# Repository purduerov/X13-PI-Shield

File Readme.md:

# Readme for X13-PI-Shield

Whenever you make a new part, download the datasheet and save it here _**and**_ with the part in the parts library

Always pull other people's changes before beginning to work
`git pull`

Be sure to push your changes after  working on them. Run:
1. `git add .` to add any files in this directory or a subdirectory
or `git add -u` to add any modified files
2. (Optional) `git clean -nX` to see what ignored files can be removed
	`git clean -fX` removes ignored files (Eagle backups)
3. `git commit -m "helpful commit message"` with a description of the work that you did
4. `git push` to push your work to github

Other helpful commands
* `git status` says information about modified and staged files
* `git log` shows the recent commits of the repository
* `git log filename.extension` show the recent commits for just that file
* `git checkout first-couple-letter-of-commit-id` lets you go back to a previous version
* `git checkout master` brings you back to the latest commit
* `git tag` lists the tags
* `git tag -a orderX -m "the version of the board placed for the X'th order"` tag a specific commit
* `git push --tags` needed to push tags to remote
* `git show orderX` show the commit log for the given tag
* `git checkout orderX` go back and interact with the files at the tagged commit

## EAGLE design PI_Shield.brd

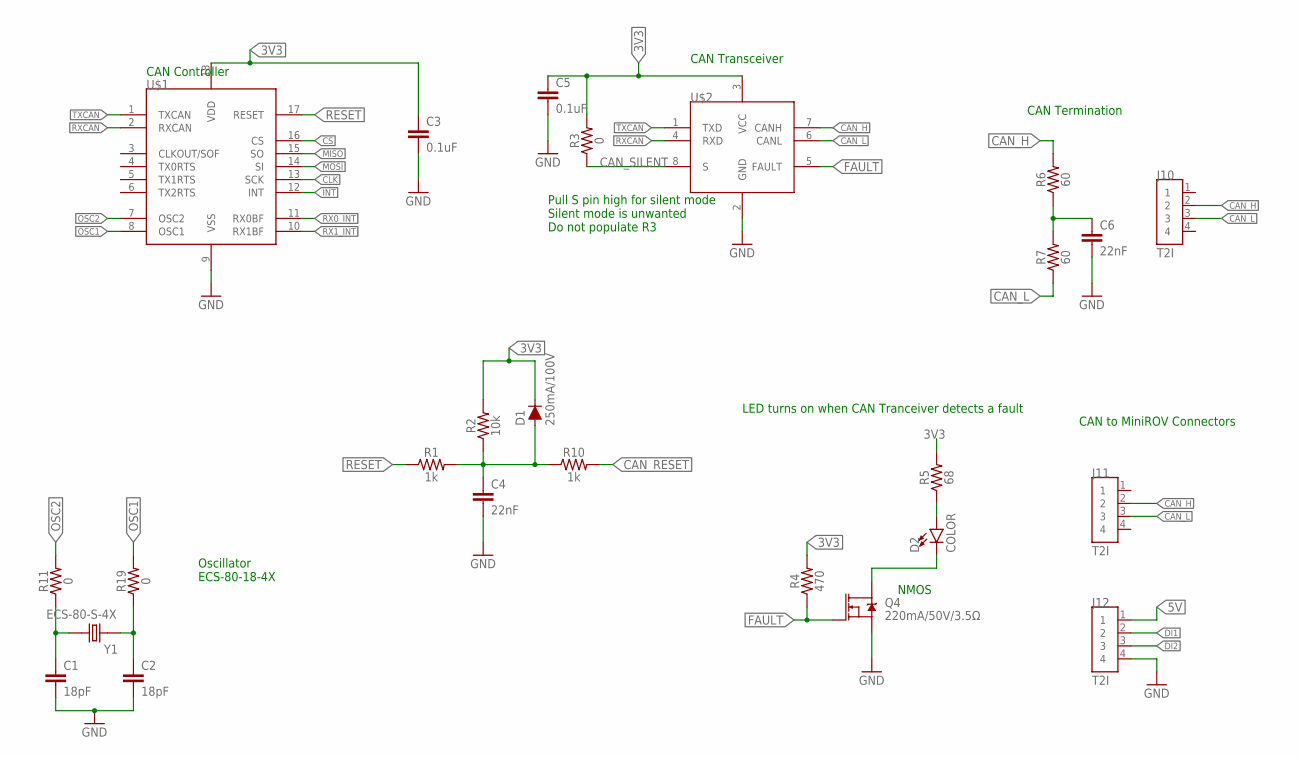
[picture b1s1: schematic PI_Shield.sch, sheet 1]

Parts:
C1, C2: 18pF; 0603
C3, C5: 0.1uF; 0603
C4, C6: 22nF; 0603
D1: 250mA/100V; SOD-323
D2: COLOR; 0805
J10, J11, J12: T2I
Q4: 220mA/50V/3.5Ω; SOT23-3
R1, R10: 1k; 0603
R2: 10k; 0603
R3, R11, R19: 0; 0603
R4: 470; 0603
R5: 68; 0603
R6, R7: 60; 0603
U$1: MCP2515; SOIC-18
U$2: TCAN337D; SOIC-8
Y1: ECS-80-S-4X; XTAL_ECS-80-S-4X

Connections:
3V3: C3.1, C5.1, D1.C, R2.2, R3.2, R4.2, R5.2, U$1.18 (VDD), U$2.3 (VCC); also elsewhere on the board
5V: J12.1; also elsewhere on the board
CAN_H: J10.2, J11.2, R6.2, U$2.7 (CANH); also elsewhere on the board
CAN_L: J10.3, J11.3, R7.1, U$2.6 (CANL); also elsewhere on the board
CAN_RESET: R10.2; also elsewhere on the board
CAN_SILENT: R3.1, U$2.8 (S)
CAN_TERM_COM: C6.1, R6.1, R7.2
CLK: U$1.13 (SCK); also elsewhere on the board
CS: U$1.16 (CS); also elsewhere on the board
DI1: J12.2; also elsewhere on the board
DI2: J12.3; also elsewhere on the board
FAULT: Q4.1 (G), R4.1, U$2.5 (FAULT)
GND: C1.2, C2.2, C3.2, C4.2, C5.2, C6.2, J12.4, Q4.2 (S), U$1.9 (VSS), U$2.2 (GND); also elsewhere on the board
INT: U$1.12 (INT); also elsewhere on the board
MISO: U$1.15 (SO); also elsewhere on the board
MOSI: U$1.14 (SI); also elsewhere on the board
unnamed: C1.1, R11.1, Y1.2
unnamed: C2.1, R19.1, Y1.1
unnamed: D2.C, Q4.3 (D)
unnamed: D2.A, R5.1
OSC1: R19.2, U$1.8 (OSC1)
OSC2: R11.2, U$1.7 (OSC2)
RESET: R1.1, U$1.17 (RESET)
RESET_MID: C4.1, D1.A, R1.2, R2.1, R10.1
RX0_INT: U$1.11 (RX0BF); also elsewhere on the board
RX1_INT: U$1.10 (RX1BF); also elsewhere on the board
RXCAN: U$1.2 (RXCAN), U$2.4 (RXD)
TXCAN: U$1.1 (TXCAN), U$2.1 (TXD)

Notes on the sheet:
Oscillator ECS-80-18-4X
CAN Termination
CAN to MiniROV Connectors
NMOS
CAN Controller
CAN Transceiver
Pull S pin high for silent mode Silent mode is unwanted Do not populate R3
LED turns on when CAN Tranceiver detects a fault

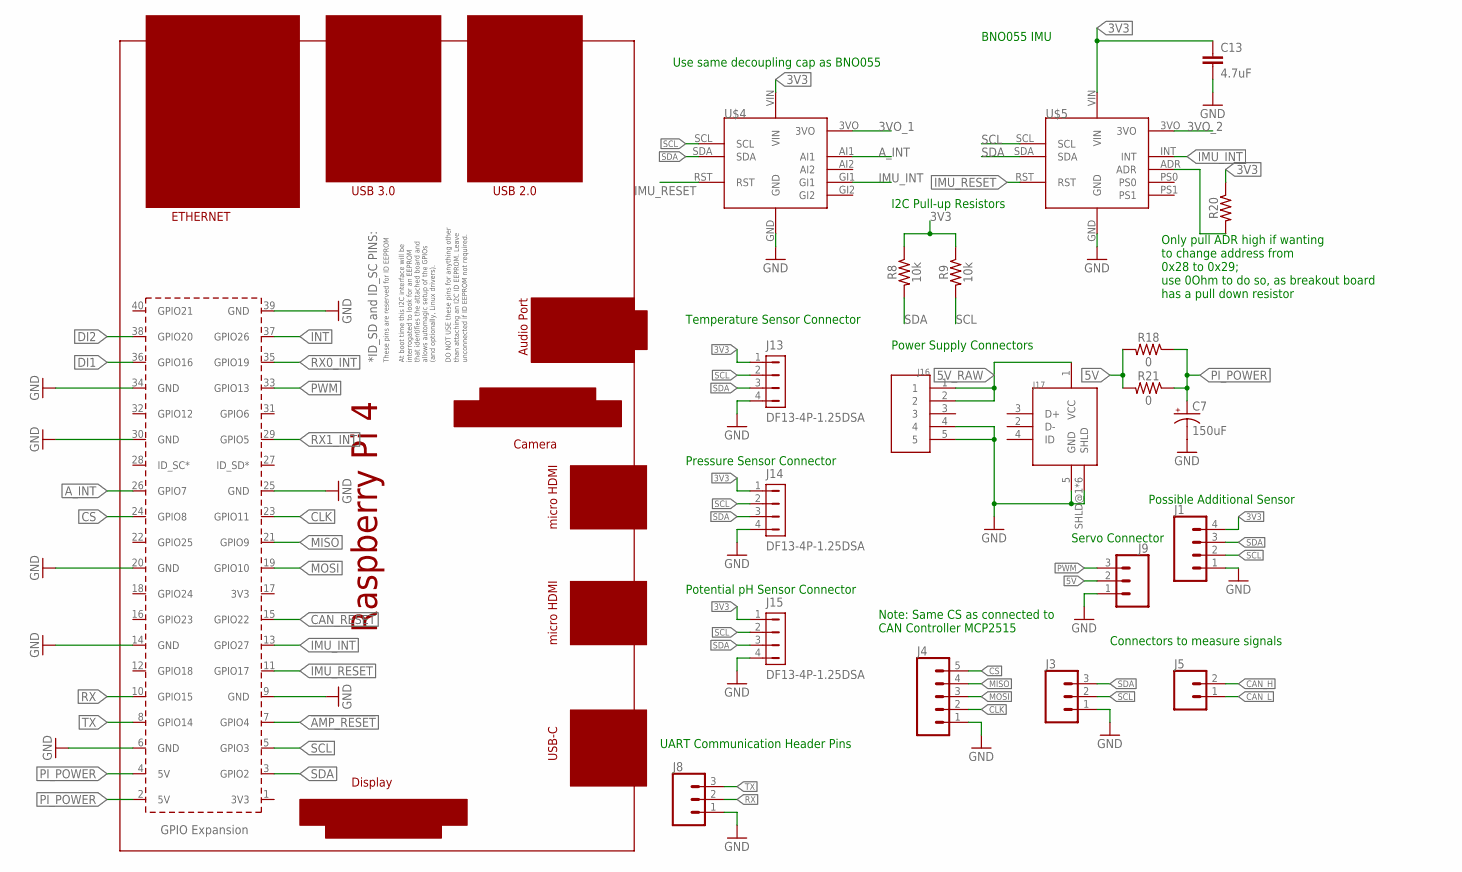
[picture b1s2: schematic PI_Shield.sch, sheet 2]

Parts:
C7: 150uF; 2917(7343-31-METRIC)
C13: 4.7uF; 0603
J1: CONN_04; 1X04
J3, J8, J9: CONN_03; 1X03
J4: CONN_05; 1X05
J5: CONN_02; 1X02
J13, J14, J15: DF13-4P-1.25DSA
J16: T2I5P
J17: USB-MICRO; MICRO-USB
R8, R9: 10k; 0603
R18, R21: 0; 0603
R20: RESISTOR0603; 0603
U$4: ADAFRUIT-FXOS8700-FXAS21002
U$5: ADAFRUIT-BNO055
U$8: RPI4

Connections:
3V3: C13.1, J1.4, J13.1, J14.1, J15.1, R8.1, R9.1, R20.1, U$4.VIN, U$5.VIN; also elsewhere on the board
3VO_1: U$4.3VO
3VO_2: U$5.3VO
5V: J9.2, R18.2, R21.2; also elsewhere on the board
5V_RAW: J16.1, J16.2, J17.1 (VCC); also elsewhere on the board
!AMP_RESET: U$8.7 (GPIO4); also elsewhere on the board
A_INT: U$4.AI1, U$8.26 (GPIO7)
CAN_H: J5.2; also elsewhere on the board
CAN_L: J5.1; also elsewhere on the board
CAN_RESET: U$8.15 (GPIO22); also elsewhere on the board
CLK: J4.2, U$8.23 (GPIO11); also elsewhere on the board
CS: J4.5, U$8.24 (GPIO8); also elsewhere on the board
DI1: U$8.36 (GPIO16); also elsewhere on the board
DI2: U$8.38 (GPIO20); also elsewhere on the board
GND: C7.-, C13.2, J1.1, J3.1, J4.1, J8.1, J9.1, J13.4, J14.4, J15.4, J16.4, J16.5, J17.5 (GND), J17.SHLD@1 (SHLD), J17.SHLD@2 (SHLD), J17.SHLD@3 (SHLD), J17.SHLD@4 (SHLD), J17.SHLD@5 (SHLD), J17.SHLD@6 (SHLD), U$4.GND, U$5.GND, U$8.6 (GND), U$8.9 (GND), U$8.14 (GND), U$8.20 (GND), U$8.25 (GND), U$8.30 (GND), U$8.34 (GND), U$8.39 (GND); also elsewhere on the board
IMU_INT: U$4.GI1, U$5.INT, U$8.13 (GPIO27)
IMU_RESET: U$4.RST, U$5.RST, U$8.11 (GPIO17)
INT: U$8.37 (GPIO26); also elsewhere on the board
MISO: J4.4, U$8.21 (GPIO9); also elsewhere on the board
MOSI: J4.3, U$8.19 (GPIO10); also elsewhere on the board
unnamed: R20.2, U$5.ADR
PI_POWER: C7.+, R18.1, R21.1, U$8.2 (5V), U$8.4 (5V)
PWM: J9.3, U$8.33 (GPIO13)
RX: J8.2, U$8.10 (GPIO15)
RX0_INT: U$8.35 (GPIO19); also elsewhere on the board
RX1_INT: U$8.29 (GPIO5); also elsewhere on the board
SCL: J1.2, J3.2, J13.2, J14.2, J15.2, R9.2, U$4.SCL, U$5.SCL, U$8.5 (GPIO3); also elsewhere on the board
SDA: J1.3, J3.3, J13.3, J14.3, J15.3, R8.2, U$4.SDA, U$5.SDA, U$8.3 (GPIO2); also elsewhere on the board
TX: J8.3, U$8.8 (GPIO14)

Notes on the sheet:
Connectors to measure signals
Temperature Sensor Connector
Pressure Sensor Connector
Potential pH Sensor Connector
BNO055 IMU
Power Supply Connectors
Possible Additional Sensor
UART Communication Header Pins
Servo Connector
Only pull ADR high if wanting to change address from 0x28 to 0x29; use 0Ohm to do so, as breakout board has a pull down resistor
Use same decoupling cap as BNO055
I2C Pull-up Resistors
Note: Same CS as connected to CAN Controller MCP2515

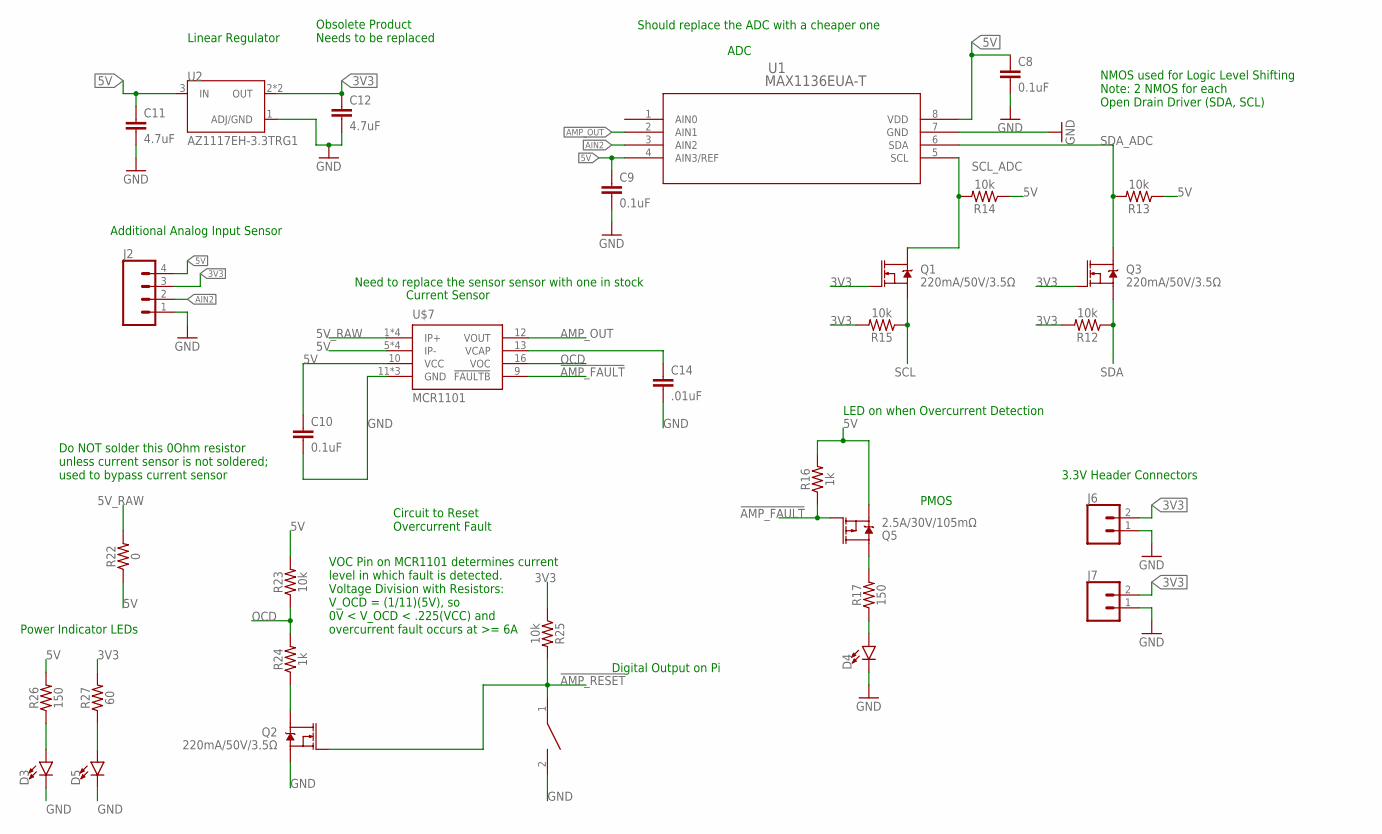
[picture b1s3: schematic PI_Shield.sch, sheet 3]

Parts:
C8, C9, C10: 0.1uF; 0603
C11, C12: 4.7uF; 0603
C14: .01uF; 0603
D3, D4, D5: LED0603; LED-0603
J2: CONN_04; 1X04
J6, J7: CONN_02; 1X02
Q1, Q2, Q3: 220mA/50V/3.5Ω; SOT23-3
Q5: 2.5A/30V/105mΩ; SOT23-3
R12, R13, R14, R15, R23, R25: 10k; 0603
R16, R24: 1k; 0603
R17, R26: 150; 0603
R22: 0; 0603
R27: 60; 0603
U1: MAX1136EUA-T; 21-0036K
U2: AZ1117EH-3.3TRG1; SOT230P700X180-4N
U$6: DISCRETECOMPONENTS_SWITCH; DISCRETECOMPONENTS_SW_2512
U$7: MCR1101; SOIC-16

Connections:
3V3: C12.1, J2.3, J6.2, J7.2, Q1.1 (G), Q3.1 (G), R12.2, R15.2, R25.1, R27.2, U2.2 (OUT), U2.4 (OUT); also elsewhere on the board
5V: C8.1, C9.1, C10.1, C11.1, J2.4, Q5.2 (S), R13.1, R14.1, R16.2, R22.1, R23.2, R26.2, U1.4 (AIN3/REF), U1.8 (VDD), U2.3 (IN), U$7.5 (IP-), U$7.6 (IP-), U$7.7 (IP-), U$7.8 (IP-), U$7.10 (VCC); also elsewhere on the board
5V_RAW: R22.2, U$7.1 (IP+), U$7.2 (IP+), U$7.3 (IP+), U$7.4 (IP+); also elsewhere on the board
!AMP_FAULT: Q5.1 (G), R16.1, U$7.9 (!FAULTB)
!AMP_RESET: Q2.1 (G), R25.2, U$6.1; also elsewhere on the board
AIN2: J2.2, U1.3 (AIN2)
AMP_OUT: U1.2 (AIN1), U$7.12 (VOUT)
GND: C8.2, C9.2, C10.2, C11.2, C12.2, C14.2, D3.C, D4.C, D5.C, J2.1, J6.1, J7.1, Q2.2 (S), U1.7 (GND), U2.1 (ADJ/GND), U$6.2, U$7.11 (GND), U$7.14 (GND), U$7.15 (GND); also elsewhere on the board
unnamed: C14.1, U$7.13 (VCAP)
unnamed: D3.A, R26.1
unnamed: Q5.3 (D), R17.2
unnamed: D4.A, R17.1
unnamed: D5.A, R27.1
unnamed: Q2.3 (D), R24.1
OCD: R23.1, R24.2, U$7.16 (VOC)
SCL: Q1.2 (S), R15.1; also elsewhere on the board
SCL_ADC: Q1.3 (D), R14.2, U1.5 (SCL)
SDA: Q3.2 (S), R12.1; also elsewhere on the board
SDA_ADC: Q3.3 (D), R13.2, U1.6 (SDA)

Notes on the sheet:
ADC
Additional Analog Input Sensor
3.3V Header Connectors
PMOS
LED on when Overcurrent Detection
NMOS used for Logic Level Shifting Note: 2 NMOS for each Open Drain Driver (SDA, SCL)
Linear Regulator
Do NOT solder this 0Ohm resistor unless current sensor is not soldered; used to bypass current sensor
Current Sensor
Circuit to Reset Overcurrent Fault
Need to replace the sensor sensor with one in stock
Should replace the ADC with a cheaper one
Obsolete Product Needs to be replaced
Power Indicator LEDs
VOC Pin on MCR1101 determines current level in which fault is detected. Voltage Division with Resistors: V_OCD = (1/11)(5V), so 0V < V_OCD < .225(VCC) and overcurrent fault occurs at >= 6A
Digital Output on Pi

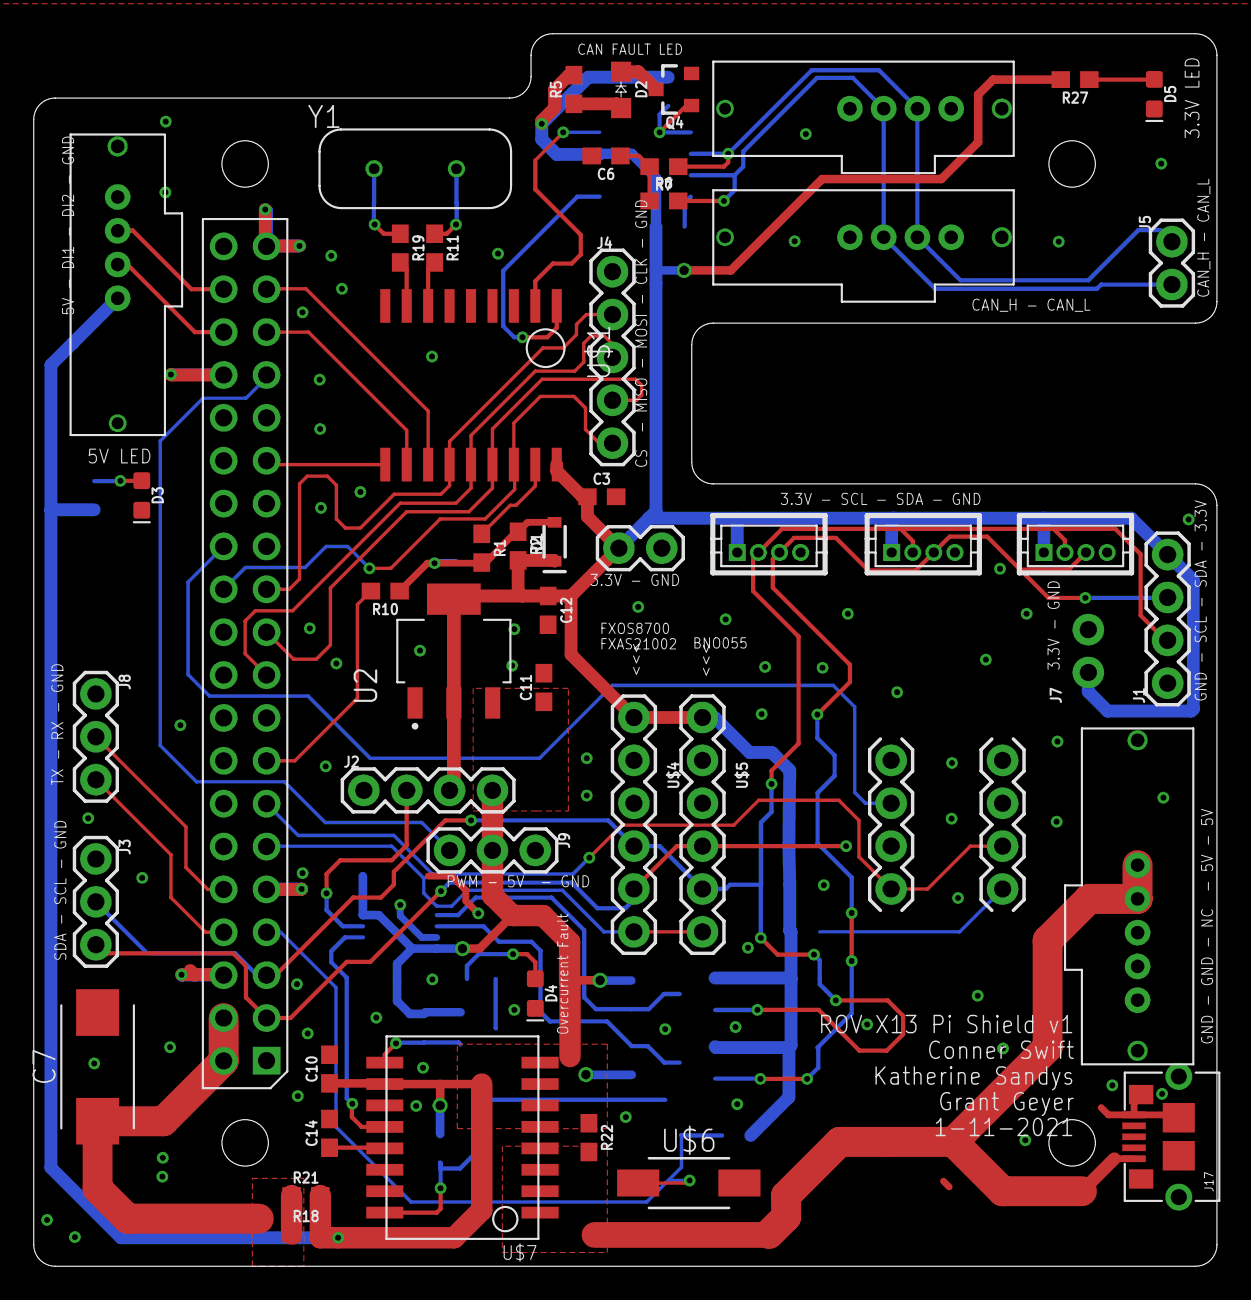
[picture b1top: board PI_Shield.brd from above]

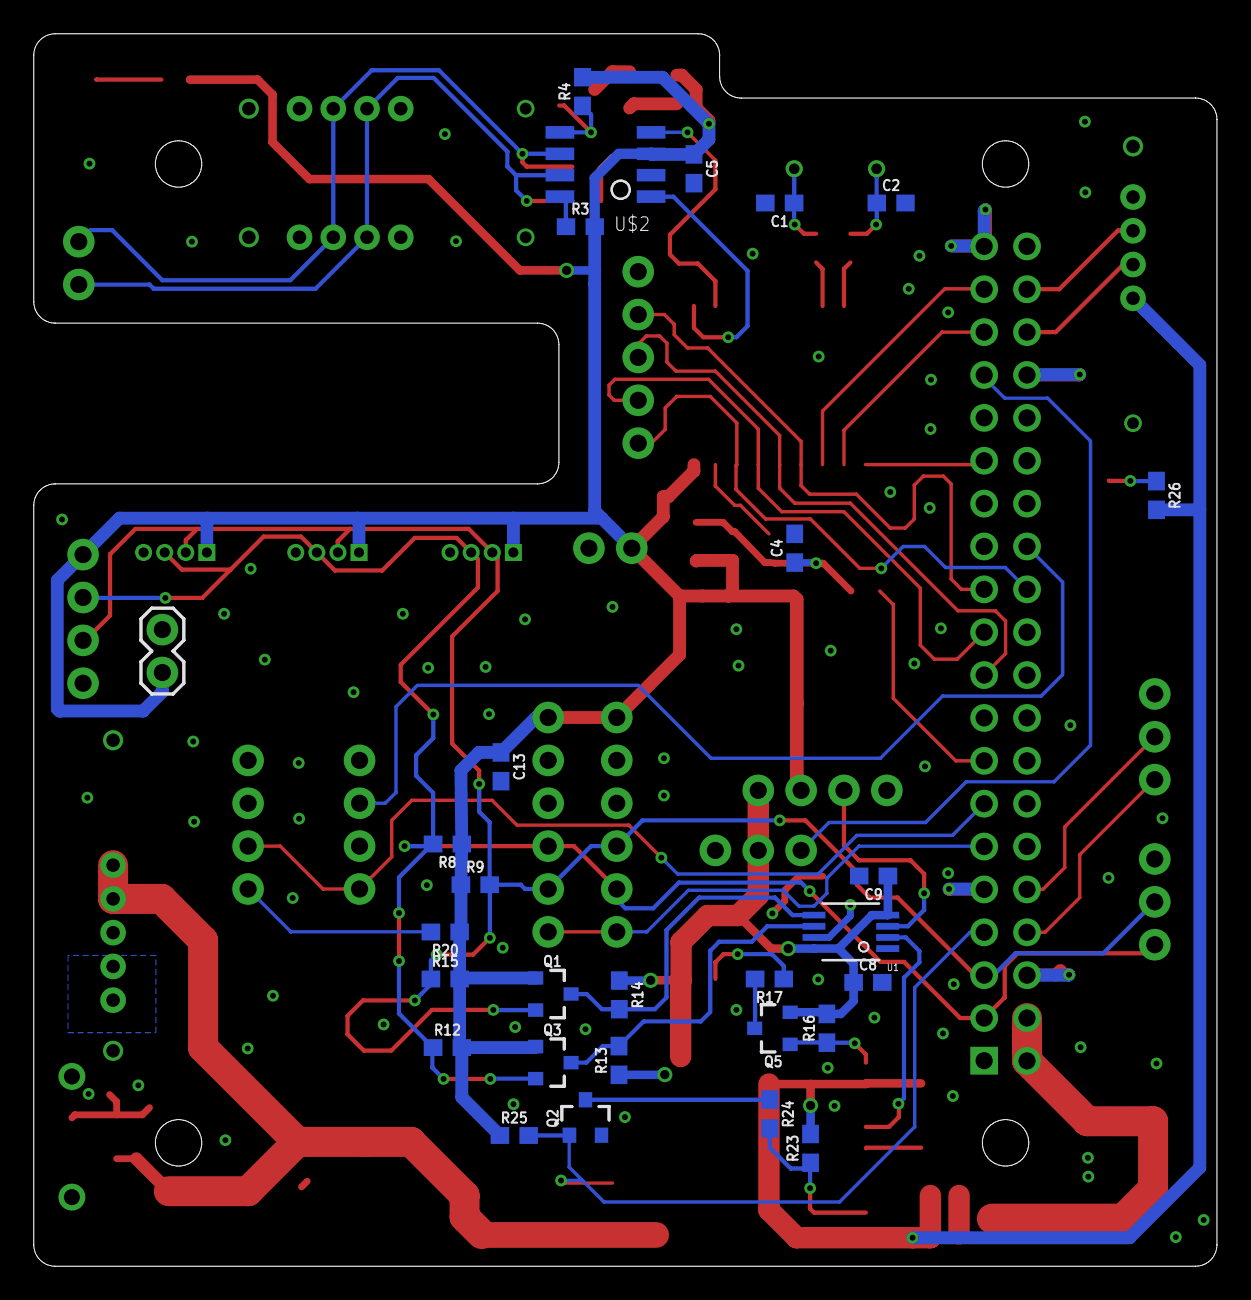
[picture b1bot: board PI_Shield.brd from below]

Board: 2 copper layers, 70.1 x 73.0 mm, 78 parts (29 on the bottom side), 52 nets.

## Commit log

2020-09-18 setup of repo
2020-12-12 schematic touch ups, new IMU, smaller board
2020-12-12 add micro usb connector for external powering while testing
2020-12-12 update bno055 footprint
2021-01-08 Added Part Datasheets and Pi 4 DXF Model
2021-01-08 Added Pi 4 and Current Sensor; Routed Interrupt pins signals to Pi
2021-01-08 Started layout
2021-01-09 Continuing Layout
2021-01-09 Finished Layout
2021-01-09 Started routing
2021-01-09 routed some
2021-01-10 General routing complete
2021-01-10 Working on Impedance Matching
2021-01-11 labels, routing touch ups, etc
2021-01-11 Finishing touches
2021-01-11 Added Image
2021-01-11 Ordering text, step, and pdf
2021-01-12 naming USB connector and add notes for next year of which ICs to replace
2021-01-20 Fixed Swapped IMUs on Schematic
2021-01-20 Updated Parts from Updated X13 Parts Library
2021-01-20 Added more notes to schematic
2021-01-20 Fix misprint on schematic
2021-02-20 Move USB connector for accessbility and shrink left side for more clearance
2021-02-20 Added Resistor Values to Power Indicator LED circuits

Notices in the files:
parts and their libraries:
SparkFun-Capacitors: Licensing: Creative Commons ShareAlike 4.0 International - https://creativecommons.org/licenses/by-sa/4.0
